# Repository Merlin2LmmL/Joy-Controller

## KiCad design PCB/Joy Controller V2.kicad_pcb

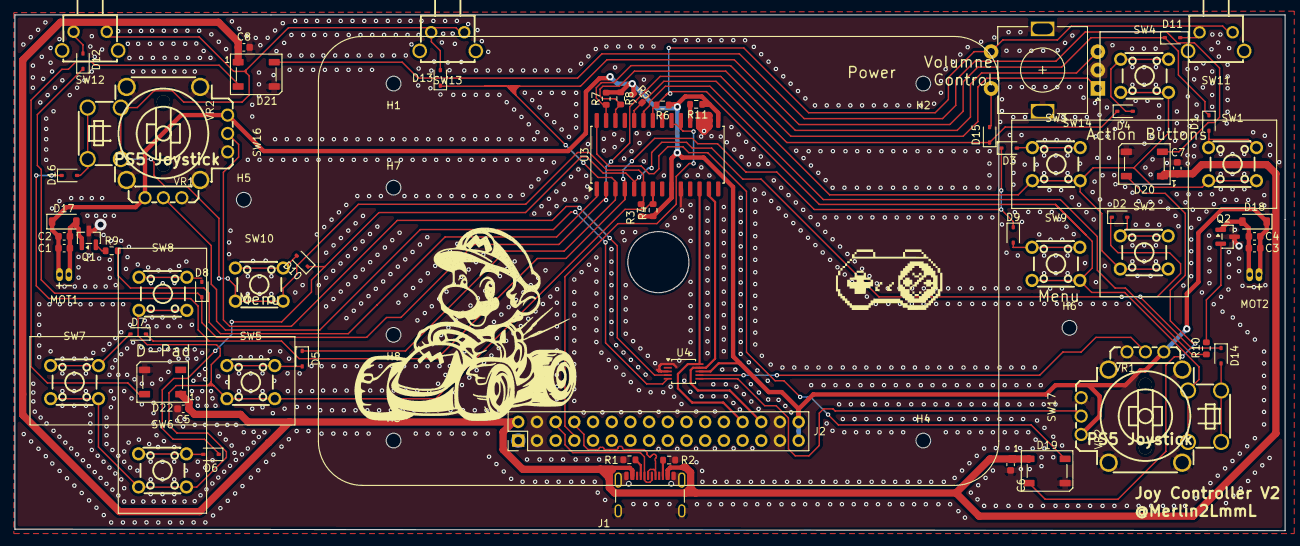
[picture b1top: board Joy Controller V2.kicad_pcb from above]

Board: 2 copper layers, 172.6 x 70.1 mm, 73 parts (0 on the bottom side), 52 nets.

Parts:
C1, C3: 1uF; C_0603_1608Metric
C2, C4, C5, C6, C7, C8: 100nF; C_0603_1608Metric
D1, D2, D3, D4, D5, D6, D7, D8, D9, D10, D11, D12, D13, D14, D15, D16: D; D_SOD-323
D17, D18: 1N4148W; D_SOD-123
D19, D20, D21, D22: WS2812B; LED_WS2812B_PLCC4_5.0x5.0mm_P3.2mm
H1, H2, H3, H4, H5, H6, H7, H8: MountingHole; MountingHole_2mm
J1: USB_C_Receptacle_USB2.0_16P; USB_C_Receptacle_GCT_USB4105-xx-A_16P_TopMnt_Horizontal
J2: Conn_02x16_Odd_Even; PinHeader_2x16_P2.54mm_Vertical
MOT1, MOT2: LCM1027A2445F; VIBRATING-MOTOR-SMD_WELDING
Q1, Q2: NPN; SOT-23
R1, R2: 5.1K; R_0603_1608Metric
R3, R4, R5, R6, R7, R8, R11: 10K; R_0603_1608Metric
R9, R10: 1K; R_0603_1608Metric
SW1, SW2, SW3, SW4, SW5, SW6, SW7, SW8, SW9, SW10: B3F-1070; SW-TH_4P-L6.2-W6.2-P4.50-LS6.5
SW11, SW12, SW13: B3F-3152; KEY-TH_4P-L7.3-W10.2-P4.50-LS7.0
SW14: RotaryEncoder_Switch_MP; RotaryEncoder_Alps_EC11E-Switch_Vertical_H20mm
SW16, SW17: RKJXV1224005; SW-TH_RKJXV1224005
U3: MCP23017_SO; SOIC-28W_7.5x17.9mm_P1.27mm
U4: ADS1015IDGS; TSSOP-10_3x3mm_P0.5mm

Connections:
+3.3V: C1.2, C2.2, C3.2, C4.2, D17.1 (K), D18.1 (K), J2.31, J2.32, MOT1.2 (+), MOT2.2 (+), R3.1, R4.1, R5.1, R6.1, R7.1, R8.1, R11.2, SW16.1 (B), SW16.6 (B), SW17.1 (B), SW17.6 (B), U3.9 (VDD), U3.15 (A0), U4.8 (VDD)
+5V: C5.1, C6.1, C7.1, C8.1, D19.1 (VDD), D20.1 (VDD), D21.1 (VDD), D22.1 (VDD), J1.A4 (VBUS), J1.A9 (VBUS), J1.B4 (VBUS), J1.B9 (VBUS), J2.2
COL0: R6.2, SW11.3, U3.22 (GPA1)
COL1: R5.2, SW1.3, SW1.4, SW2.3, SW2.4, SW3.3, SW3.4, SW4.3, SW4.4, U3.24 (GPA3)
COL2: R4.2, SW5.3, SW5.4, SW7.3, SW7.4, SW8.3, SW8.4, U3.7 (GPB6)
COL3: R3.2, SW13.3, U3.6 (GPB5)
DN: J1.A7 (D-), J1.B7 (D-), J2.6
DP: J1.A6 (D+), J1.B6 (D+), J2.8
EC11+: SW9.3, SW9.4, SW11.4, SW14.S1, SW17.a, SW17.c
EC11-: D15.2 (A), SW14.S2
GND: C5.2, C6.2, C7.2, C8.2, D19.3 (VSS), D20.3 (VSS), D21.3 (VSS), D22.3 (VSS), J1.A1 (GND), J1.A12 (GND), J1.B1 (GND), J1.B12 (GND), J1.S1 (SHIELD), J2.3, J2.4, J2.29, J2.30, Q1.3 (E), Q2.3 (E), R1.2, R2.2, SW14.C, SW14.MP, SW16.3 (A), SW16.4 (A), SW16.7 (GND), SW16.8 (GND), SW16.9 (GND), SW16.10 (GND), SW17.3 (A), SW17.4 (A), SW17.7 (GND), SW17.8 (GND), SW17.9 (GND), SW17.10 (GND), U3.10 (VSS), U3.16 (A1), U3.17 (A2), U4.1 (ADDR), U4.3 (GND)
GPIO38: J2.7, U3.19 (INTB), U3.20 (INTA)
JOY_L_VRx: SW16.5 (DTA), U4.4 (AIN0)
JOY_L_VRy: SW16.2 (DTA), U4.5 (AIN1)
JOY_R_VRx: SW17.5 (DTA), U4.6 (AIN2)
JOY_R_VRy: SW17.2 (DTA), U4.7 (AIN3)
JOY_SW_L+: SW10.3, SW10.4, SW12.3, SW12.4, SW13.4, SW16.a, SW16.c
JOY_SW_L-: D16.2 (A), SW16.b, SW16.d
JOY_SW_R-: D14.2 (A), SW17.b, SW17.d
LEDs: D19.4 (DIN), U3.28 (GPA7)
M_HAP_L: R9.2, U3.1 (GPB0)
M_HAP_R: R10.2, U3.23 (GPA2)
unnamed: D1.2 (A), SW1.1, SW1.2
unnamed: D2.2 (A), SW2.1, SW2.2
unnamed: D3.2 (A), SW3.1, SW3.2
unnamed: D4.2 (A), SW4.1, SW4.2
unnamed: D5.2 (A), SW5.1, SW5.2
unnamed: D7.2 (A), SW7.1, SW7.2
unnamed: D8.2 (A), SW8.1, SW8.2
unnamed: D9.2 (A), SW9.1, SW9.2
unnamed: D10.2 (A), SW10.1, SW10.2
unnamed: D11.2 (A), SW11.1, SW11.2
unnamed: D12.2 (A), SW12.1, SW12.2
unnamed: D13.2 (A), SW13.1, SW13.2
unnamed: C1.1, C2.1, D17.2 (A), MOT1.1 (-), Q1.1 (C)
unnamed: C3.1, C4.1, D18.2 (A), MOT2.1 (-), Q2.1 (C)
unnamed: D19.2 (DOUT), D20.4 (DIN)
unnamed: D20.2 (DOUT), D21.4 (DIN)
unnamed: D21.2 (DOUT), D22.4 (DIN)
unnamed: J1.A5 (CC1), R1.1
unnamed: J1.B5 (CC2), R2.1
unnamed: Q1.2 (B), R9.1
unnamed: Q2.2 (B), R10.1
unnamed: R11.1, U3.18 (~RESET)
ROT_ENC_A: R8.2, SW14.A, U3.26 (GPA5)
ROT_ENC_B: R7.2, SW14.B, U3.27 (GPA6)
ROW0: D1.1 (K), D5.1 (K), D11.1 (K), D13.1 (K), U3.3 (GPB2)
ROW1: D2.1 (K), D6.1 (K_1), D10.1 (K), D14.1 (K), U3.5 (GPB4)
ROW2: D3.1 (K), D7.1 (K), D9.1 (K), D16.1 (K), U3.4 (GPB3)
ROW3: D4.1 (K), D8.1 (K), D12.1 (K), D15.1 (K), U3.2 (GPB1)
SCL(GPIO7): J2.26, U3.12 (SCK), U4.10 (SCL)
SDA(GPIO8): J2.28, U3.13 (SDA), U4.9 (SDA)

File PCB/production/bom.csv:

Designator,Footprint,Quantity,Value,LCSC Part #
"C1, C3",0603,2,1uF,
"C2, C4, C5, C6, C7, C8",0603,6,100nF,
"D1, D10, D11, D12, D13, D14, D15, D16, D2, D3, D4, D5, D6, D7, D8, D9",D_SOD-323,16,D,
"D17, D18",D_SOD-123,2,1N4148W,
"D19, D20, D21, D22",LED_WS2812B_PLCC4_5.0x5.0mm_P3.2mm,4,WS2812B,
J1,USB_C_Receptacle_GCT_USB4105-xx-A_16P_TopMnt_Horizontal,1,USB_C_Receptacle_USB2.0_16P,
J2,PinHeader_2x16_P2.54mm_Vertical,1,Conn_02x16_Odd_Even,
"MOT1, MOT2",VIBRATING-MOTOR-SMD_WELDING,2,LCM1027A2445F,C2759984
"Q1, Q2",SOT-23,2,NPN,
"R1, R2",0603,2,5.1K,
"R10, R9",0603,2,1K,
"R11, R3, R4, R5, R6, R7, R8",0603,7,10K,
"SW1, SW10, SW2, SW3, SW4, SW5, SW6, SW7, SW8, SW9",SW_TH_Tactile_Omron_B3F-107x,10,SW_Push,
"SW11, SW12, SW13",SW_SPST_Omron_B3F-315x_Angled,3,SW_Push,
SW14,RotaryEncoder_Alps_EC11E-Switch_Vertical_H20mm,1,RotaryEncoder_Switch_MP,
"U1, U2",JOYSTICK,2,COM-09032,
U3,SOIC-28W_7.5x17.9mm_P1.27mm,1,MCP23017_SO,
U4,TSSOP-10_3x3mm_P0.5mm,1,ADS1015IDGS,

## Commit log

2026-03-26 Revert "Add files via upload" to wrong branch
    This reverts commit cd919539d543d6e745dfcf359e1c6175077a8b17.
